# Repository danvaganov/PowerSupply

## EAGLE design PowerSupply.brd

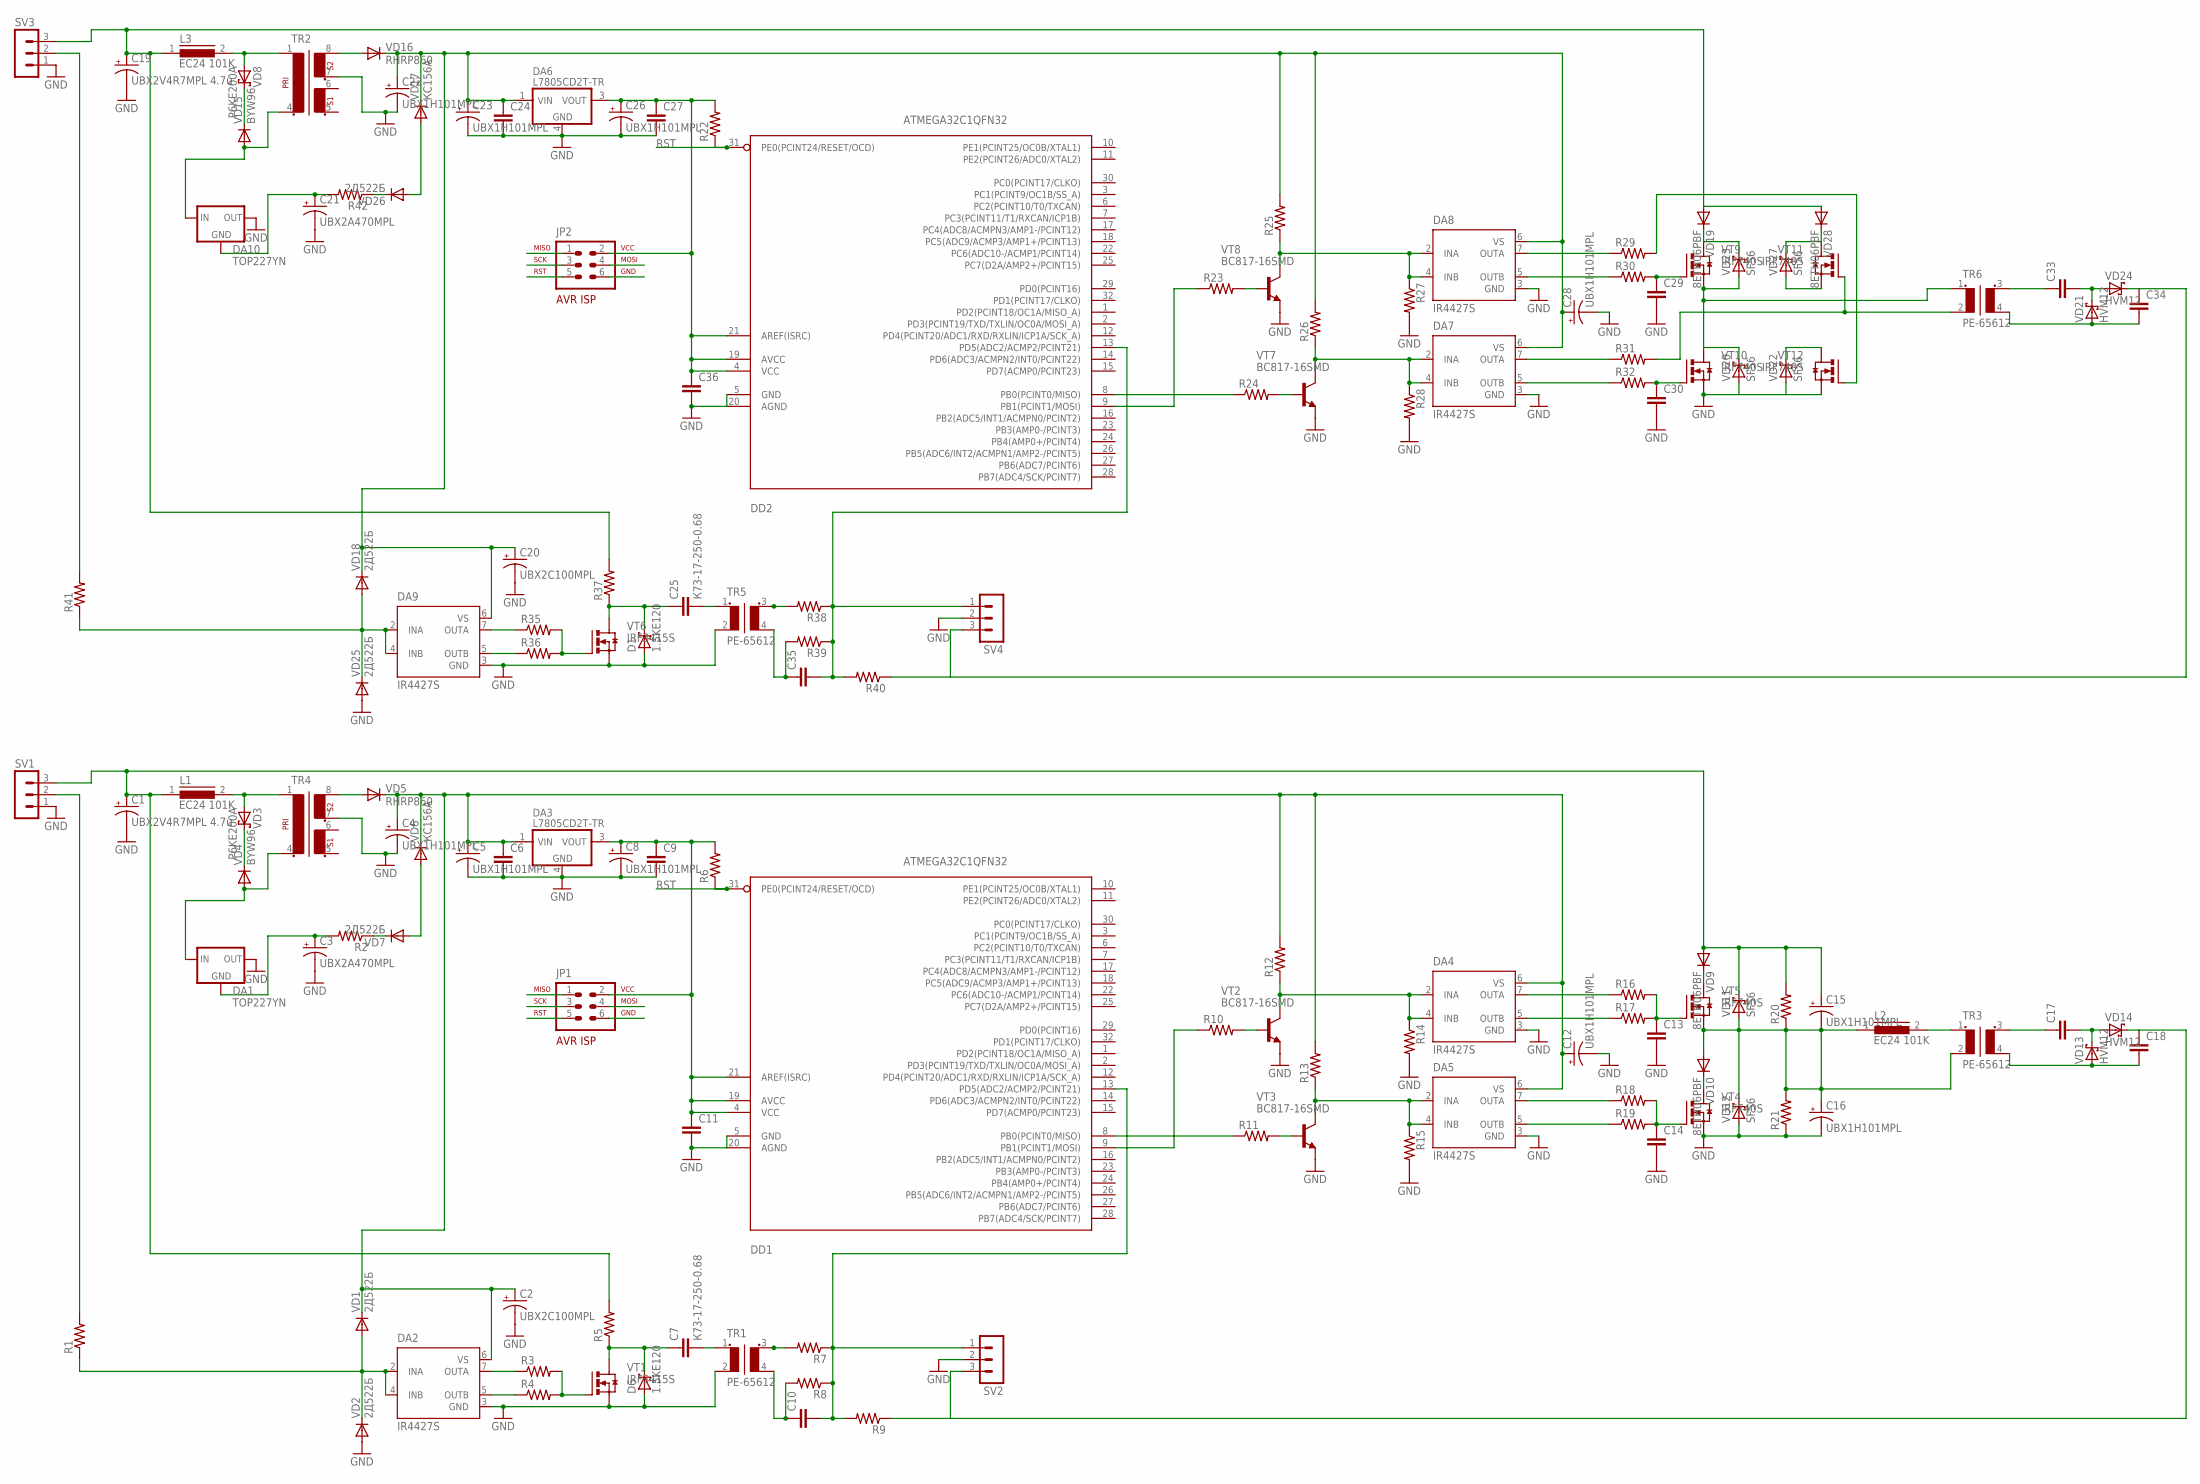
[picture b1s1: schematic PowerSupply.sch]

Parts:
C1, C19: UBX2V4R7MPL 4.7u; CPOL-RADIAL-100UF-25V
C2, C20: UBX2C100MPL; CPOL-RADIAL-100UF-25V
C3, C21: UBX2A470MPL; CPOL-RADIAL-100UF-25V
C4, C5, C8, C12, C15, C16, C22, C23, C26, C28: UBX1H101MPL; CPOL-RADIAL-100UF-25V
C6, C9, C10, C11, C13, C14, C24, C27, C29, C30, C35, C36: CAP1206; 1206
C7, C25: К73-17-250-0.68; CAP-PTH-LARGE
C17, C18, C33, C34: CC1812; C1812
D1, D6: 1.5KE120; CB417-15
DA1, DA10: TOP227YN; TO220S
DA2, DA4, DA5, DA7, DA8, DA9: IR4427S; SO08
DA3, DA6: L7805CD2T-TR; D2PAK-3
DD1, DD2: ATMEGA32C1QFN32; QFN32
JP1, JP2: AVR-ISP-6VERT; AVR-ISP-6
L1, L2, L3: EC24 101K; MMICC7
R1, R2, R3, R4, R5, R6, R7, R8, R9, R10, R11, R12, R13, R14, R15, R16, R17, R18, R19, R20, R21, R22, R23, R24, R25, R26, R27, R28, R29, R30, R31, R32, R35, R36, R37, R38, R39, R40, R41, R42: RESISTOR1206; 1206
SV1, SV2, SV3, SV4: MA03-1
TR1, TR3, TR5, TR6: PE-65612
TR2, TR4: EE20-2
VD1, VD2, VD7, VD18, VD25, VD26: 2Д522Б; DO35-10
VD3, VD8: P6KE200A; CB417-15
VD4, VD15: BYW96; SOD64-10
VD5, VD16: RHRP860; TO220ACS
VD6, VD17: КС156А; DO35-10
VD9, VD10, VD19, VD28: 8ETH06PBF; TO220ACS
VD11, VD12, VD20, VD22, VD23, VD27: SF56; CB417-15
VD13, VD14, VD21, VD24: HVM12; CB417-15
VT1, VT6: IRF3415S; D2PACK
VT2, VT3, VT7, VT8: BC817-16SMD; SOT23-BEC
VT4, VT5, VT9, VT10, VT11, VT12: IRF740S; D2PACK

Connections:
GND: C1.2 (-), C2.2 (-), C3.2 (-), C4.2 (-), C5.2 (-), C6.2, C8.2 (-), C9.2, C11.2, C12.2 (-), C13.2, C14.2, C16.2 (-), C19.2 (-), C20.2 (-), C21.2 (-), C22.2 (-), C23.2 (-), C24.2, C26.2 (-), C27.2, C28.2 (-), C29.2, C30.2, C36.2, D1.A, D6.A, DA1.2 (OUT), DA2.3 (GND), DA3.4 (GND), DA4.3 (GND), DA5.3 (GND), DA6.4 (GND), DA7.3 (GND), DA8.3 (GND), DA9.3 (GND), DA10.2 (OUT), DD1.5 (GND), DD1.20 (AGND), DD2.5 (GND), DD2.20 (AGND), JP1.6, JP2.6, R14.2, R15.2, R21.1, R27.2, R28.2, SV1.1, SV2.2, SV3.1, SV4.2, TR1.2, TR2.7 (5), TR4.7 (5), TR5.2, VD2.A, VD12.A, VD20.A, VD22.A, VD25.A, VT1.3 (S), VT2.E, VT3.E, VT4.3 (S), VT6.3 (S), VT7.E, VT8.E, VT10.3 (S), VT12.3 (S)
MISO: DD1.8 (PB0(PCINT0/MISO)), JP1.1, R11.1
MISO1: DD2.8 (PB0(PCINT0/MISO)), JP2.1, R24.1
MOSI: DD1.9 (PB1(PCINT1/MOSI)), JP1.4, R10.1
MOSI1: DD2.9 (PB1(PCINT1/MOSI)), JP2.4, R23.1
unnamed: TR4.8 (6), VD5.A
unnamed: TR2.8 (6), VD16.A
unnamed: DA5.2 (INA), DA5.4 (INB), R13.1, R15.1, VT3.C
unnamed: DA4.2 (INA), DA4.4 (INB), R12.1, R14.1, VT2.C
unnamed: C17.2, VD13.C, VD14.A
unnamed: C18.1, R9.1, SV2.3, VD14.C
unnamed: R10.2, VT2.B
unnamed: R11.2, VT3.B
unnamed: DA5.7 (OUTA), R18.1
unnamed: DA5.5 (OUTB), R19.1
unnamed: DA4.5 (OUTB), R17.1
unnamed: DA4.7 (OUTA), R16.1
unnamed: C14.1, R18.2, R19.2, VT4.1 (G)
unnamed: C13.1, R16.2, R17.2, VT5.1 (G)
unnamed: C18.2, TR3.4 (S2), VD13.A
unnamed: C17.1, TR3.3 (S1)
unnamed: VD9.C, VT5.2 (D)
unnamed: DA1.3 (IN), TR4.4 (2), VD4.A
unnamed: DA2.5 (OUTB), R4.1
unnamed: C15.2 (-), C16.1 (+), L2.1, R20.1, R21.2, TR3.2, VD10.A, VD11.A, VD12.C, VT5.3 (S)
unnamed: L2.2, TR3.1
unnamed: VD10.C, VT4.2 (D)
unnamed: DA2.7 (OUTA), R3.1
unnamed: DA7.2 (INA), DA7.4 (INB), R26.1, R28.1, VT7.C
unnamed: DA8.2 (INA), DA8.4 (INB), R25.1, R27.1, VT8.C
unnamed: R3.2, R4.2, VT1.1 (G)
unnamed: R2.1, VD7.C
unnamed: C2.1 (+), C4.1 (+), C5.1 (+), C6.1, C12.1 (+), DA2.6 (VS), DA3.1 (VIN), DA4.6 (VS), DA5.6 (VS), R12.2, R13.2, VD1.C, VD5.C, VD6.C
unnamed: DA2.2 (INA), DA2.4 (INB), R1.1, VD1.A, VD2.C
unnamed: C7.1, D6.C, R5.1, VT1.2 (D)
unnamed: C10.1, R8.2, TR1.4 (S2)
unnamed: C7.2, TR1.1
unnamed: R7.2, TR1.3 (S1)
unnamed: C10.2, DD1.13 (PD5(ADC2/ACMP2/PCINT21)), R7.1, R8.1, R9.2, SV2.1
unnamed: C3.1 (+), DA1.1 (GND), R2.2
unnamed: R1.2, SV1.2
unnamed: L1.2, TR4.1, VD3.A
unnamed: VD3.C, VD4.C
unnamed: C1.1 (+), C15.1 (+), L1.1, R5.2, R20.2, SV1.3, VD9.A, VD11.C
unnamed: R23.2, VT8.B
unnamed: VD6.A, VD7.A
unnamed: R24.2, VT7.B
unnamed: DA7.7 (OUTA), R31.1
unnamed: DA7.5 (OUTB), R32.1
unnamed: DA8.5 (OUTB), R30.1
unnamed: DA8.7 (OUTA), R29.1
unnamed: C30.1, R32.2, VT10.1 (G)
unnamed: C29.1, R30.2, VT9.1 (G)
unnamed: C33.2, VD21.C, VD24.A
unnamed: C34.1, R40.1, SV4.3, VD24.C
unnamed: C34.2, TR6.4 (S2), VD21.A
unnamed: C33.1, TR6.3 (S1)
unnamed: TR6.1, VD20.C, VD23.A, VT9.3 (S), VT10.2 (D)
unnamed: VD19.C, VD23.C, VT9.2 (D)
unnamed: C20.1 (+), C22.1 (+), C23.1 (+), C24.1, C28.1 (+), DA6.1 (VIN), DA7.6 (VS), DA8.6 (VS), DA9.6 (VS), R25.2, R26.2, VD16.C, VD17.C, VD18.C
unnamed: DA9.2 (INA), DA9.4 (INB), R41.1, VD18.A, VD25.C
unnamed: DA9.5 (OUTB), R36.1
unnamed: DA9.7 (OUTA), R35.1
unnamed: R35.2, R36.2, VT6.1 (G)
unnamed: C25.1, D1.C, R37.1, VT6.2 (D)
unnamed: C35.1, R39.2, TR5.4 (S2)
unnamed: C25.2, TR5.1
unnamed: R38.2, TR5.3 (S1)
unnamed: C35.2, DD2.13 (PD5(ADC2/ACMP2/PCINT21)), R38.1, R39.1, R40.2, SV4.1
unnamed: L3.2, TR2.1, VD8.A
unnamed: VD8.C, VD15.C
unnamed: C19.1 (+), L3.1, R37.2, SV3.3, VD19.A, VD28.A
unnamed: R41.2, SV3.2
unnamed: DA10.3 (IN), TR2.4 (2), VD15.A
unnamed: R42.1, VD26.C
unnamed: C21.1 (+), DA10.1 (GND), R42.2
unnamed: VD17.A, VD26.A
unnamed: VD27.C, VD28.C, VT11.2 (D)
unnamed: VD27.A, VT11.3 (S)
unnamed: VD22.C, VT12.2 (D)
unnamed: R29.2, VT12.1 (G)
unnamed: R31.2, TR6.2, VT11.1 (G)
RST: DD1.31 (PE0(PCINT24/RESET/OCD)), DD2.31 (PE0(PCINT24/RESET/OCD)), JP1.5, JP2.5, R6.1, R22.1
SCK: JP1.3
SCK1: JP2.3
VOUT: C8.1 (+), C9.1, C11.1, C26.1 (+), C27.1, C36.1, DA3.3 (VOUT), DA6.3 (VOUT), DD1.4 (VCC), DD1.19 (AVCC), DD1.21 (AREF(ISRC)), DD2.4 (VCC), DD2.19 (AVCC), DD2.21 (AREF(ISRC)), JP1.2, JP2.2, R6.2, R22.2

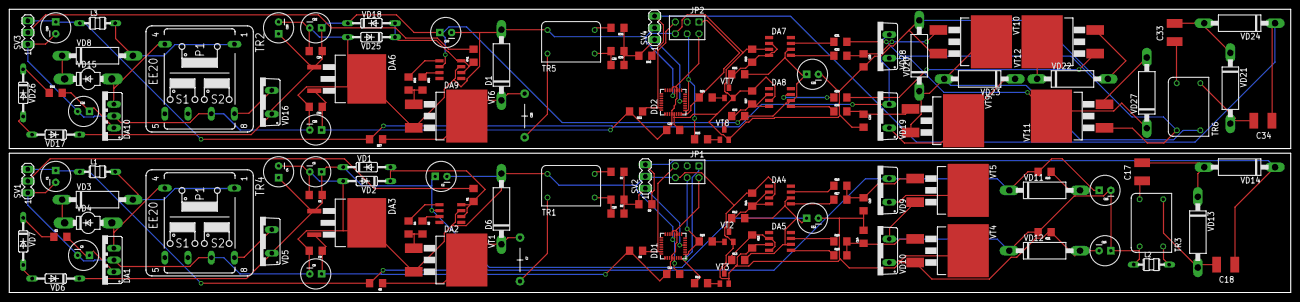
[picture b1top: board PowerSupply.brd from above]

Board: 2 copper layers, 276.0 x 61.0 mm, 143 parts (0 on the bottom side), 84 nets.

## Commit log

2014-08-20 Init 1.0.0

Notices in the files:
parts and their libraries:
SparkFun-Capacitors: Licensing: CC v3.0 Share-Alike You are welcome to use this library for commercial purposes.
